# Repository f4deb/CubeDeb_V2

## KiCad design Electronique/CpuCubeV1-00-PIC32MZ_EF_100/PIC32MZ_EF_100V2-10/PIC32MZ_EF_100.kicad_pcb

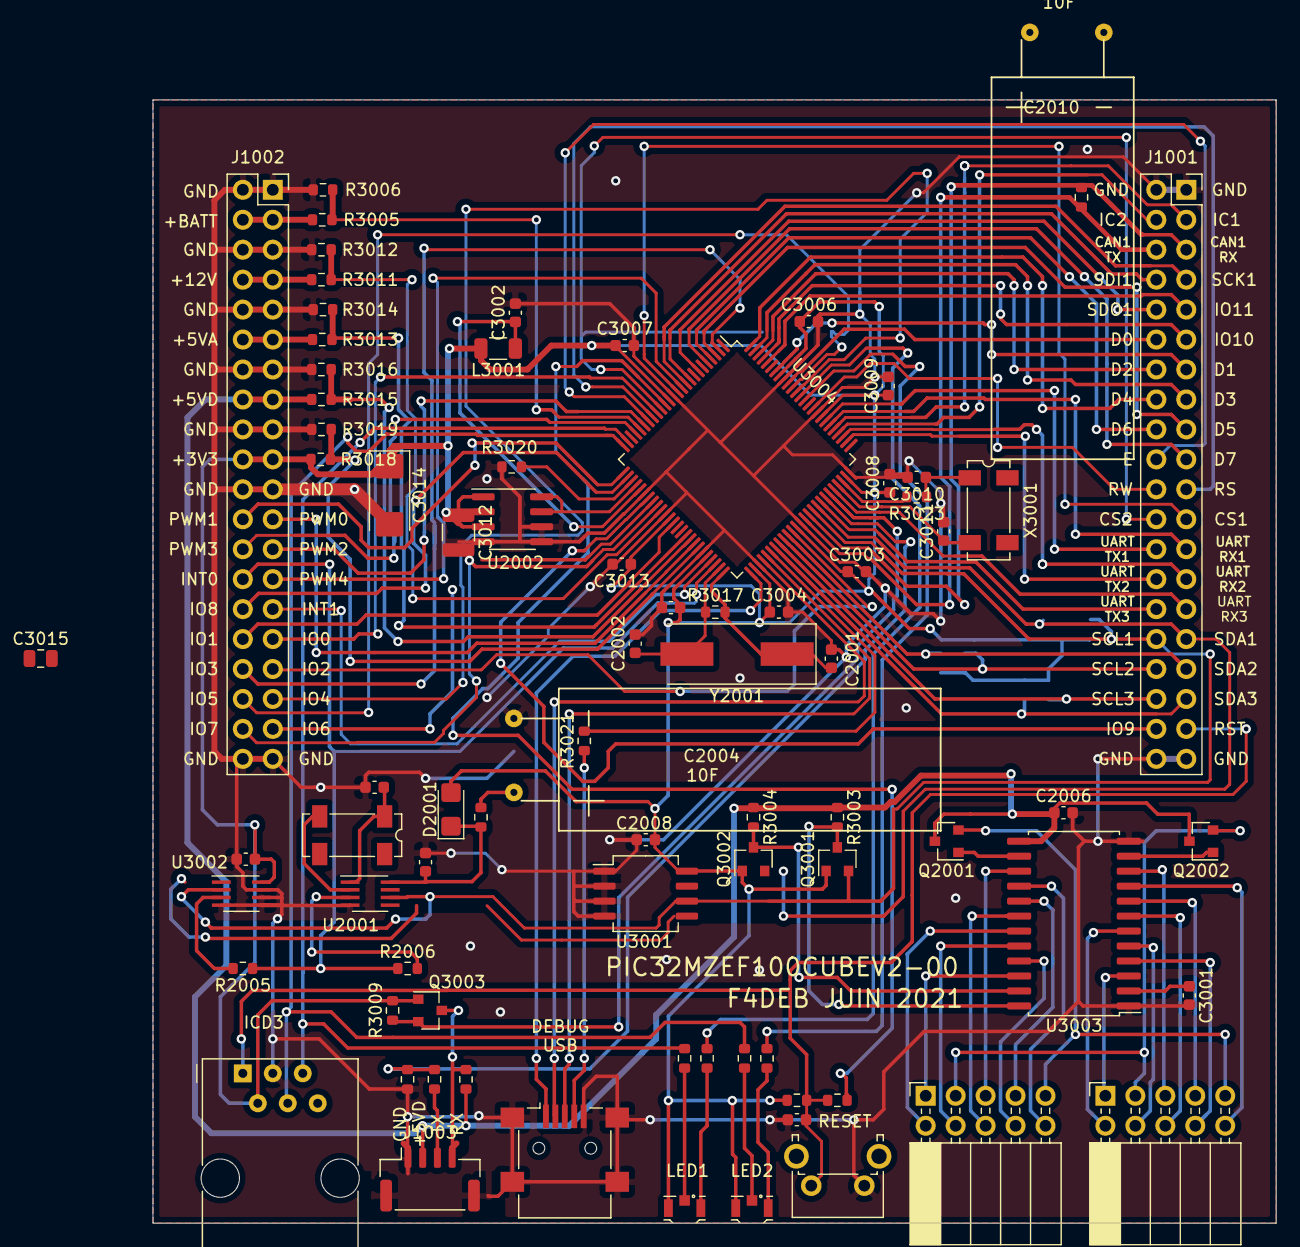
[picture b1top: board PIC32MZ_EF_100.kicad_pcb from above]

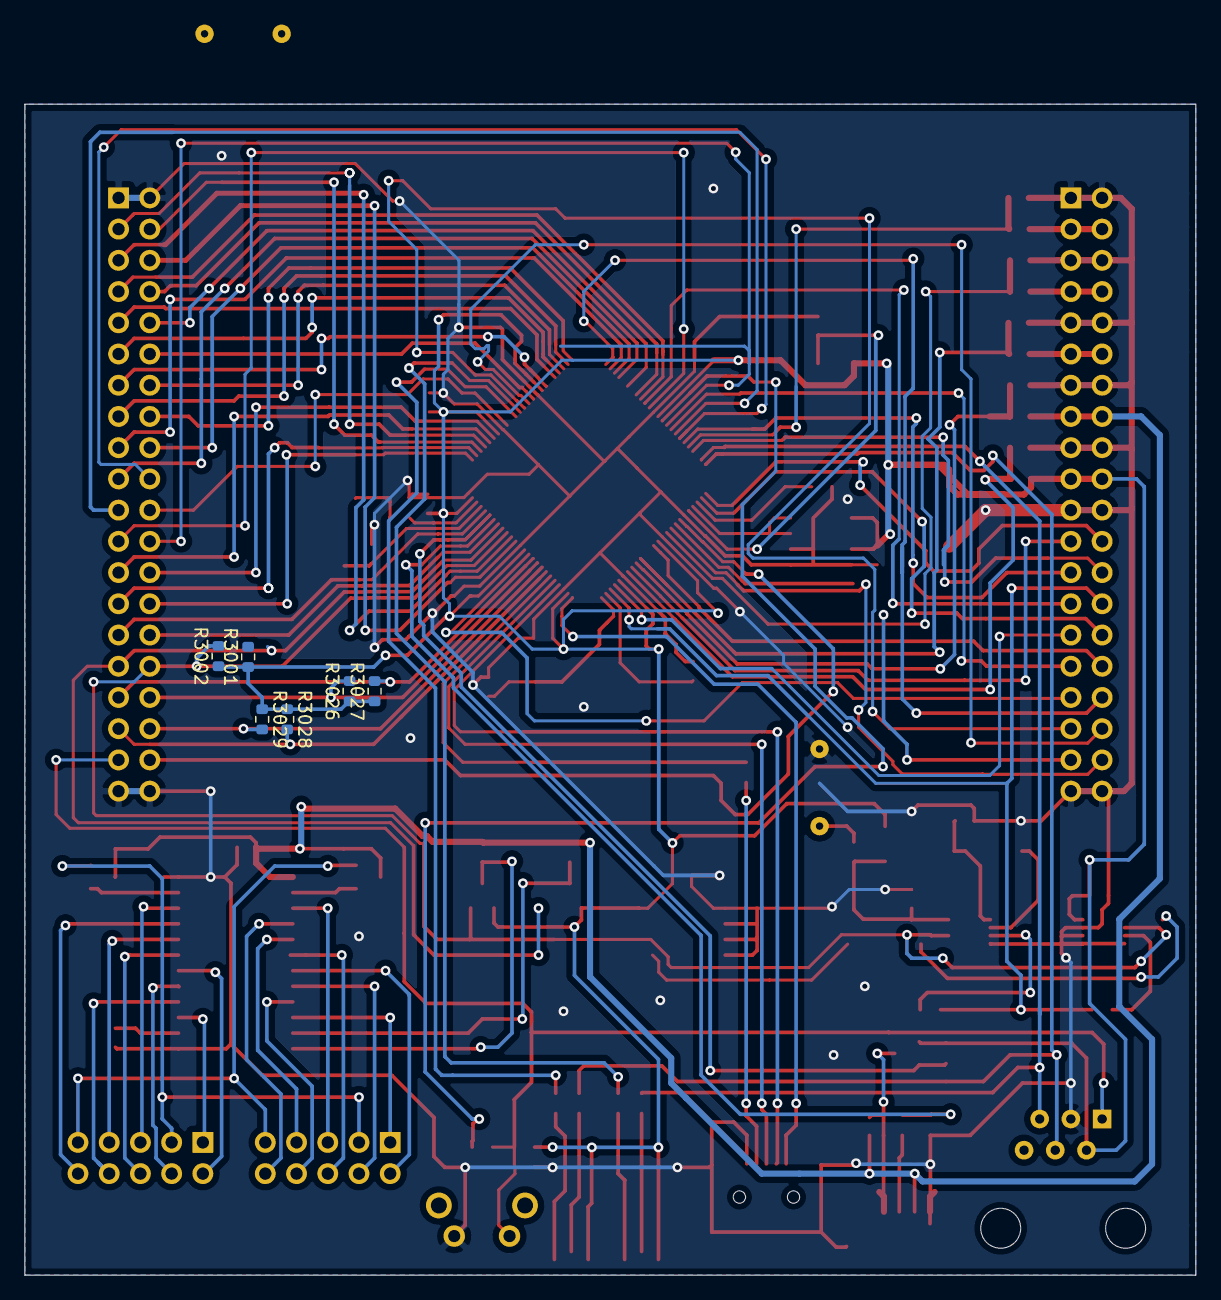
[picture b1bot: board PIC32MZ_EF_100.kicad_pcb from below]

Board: 2 copper layers, 95.2 x 95.2 mm, 87 parts (6 on the bottom side), 120 nets.

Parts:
C2001, C2002: 22p; C_0603_1608Metric
C2003: NC; C_0603_1608Metric
C2004, C2010: 10F; C-10F
C2005: 10p; C_0603_1608Metric
C2006, C2007, C2008, C2009, C3002, C3003, C3004, C3005, C3006, C3007, C3008, C3009, C3013: 100n; C_0603_1608Metric
C3001: 2.7n; C_0603_1608Metric
C3010, C3011: 33p; C_0603_1608Metric
C3012: 2.2µF; C_1210_3225Metric
C3014: 47µ; CP_EIA-6032-28_Kemet-C
C3015: 220p; C_0805_2012Metric
D1001, D1002: LED_Dual_CCA; LED_LiteOn_LTST-S326
D2001: D_Schottky; D_1206_3216Metric_Castellated
J1001, J1002: Conn_02x20_Odd_Even; PinSocket_2x20_P2.54mm_Vertical
J1003: Conn_01x04; JST_GH_SM04B-GHS-TB_1x04-1MP_P1.25mm_Horizontal
J1004: USB_B_Mini; USB_Mini-B_Lumberg_2486_01_Horizontal
J1005: RJ12; RJ12_Amphenol_54601
J2001, J2002: Conn_02x05_Top_Bottom; PinSocket_2x05_P2.54mm_Horizontal
L3001: 15µH; R_1206_3216Metric
Q2001, Q2002: BSR19; SOT-23
Q3001, Q3002, Q3003: 2N7002; SOT-23
R1001, R1002, R1003, R1004: R; R_0603_1608Metric
R2003: 330; R_0603_1608Metric
R2005, R2006, R3022: 100; R_0603_1608Metric
R3001, R3002: 4.7k; R_0603_1608Metric
R3003, R3004: 2.2k; R_0603_1608Metric
R3005, R3009, R3010, R3011, R3013, R3015, R3018, R3025: 10k; R_0603_1608Metric
R3006, R3008, R3012: 1k5; R_0603_1608Metric
R3007: 1k; R_0603_1608Metric
R3014, R3016, R3019: 4k7; R_0603_1608Metric
R3017: 1M; R_0603_1608Metric
R3020, R3021: 0; R_0603_1608Metric
R3023: 2k2; R_0603_1608Metric
R3024: 120; R_0603_1608Metric
R3026, R3027, R3028, R3029: 2k1; R_0603_1608Metric
SW1001: SW_Push; SW_Tactile_SPST_Angled_PTS645Vx58-2LFS
U2001: PCF8563T; SSOP-8_2.95x2.8mm_P0.65mm
U2002: MCP1501-SN; SOIC-8_3.9x4.9mm_P1.27mm
U3001: 24LC1025; SO-8_5.3x6.2mm_P1.27mm
U3002: LM75A; SSOP-8_2.95x2.8mm_P0.65mm
U3003: SAA1064T; SOIC-24W_7.5x15.4mm_P1.27mm
U3004: PIC32MZ2048EF100; TQFP-100_14x14mm_P0.5mm
X3001: 32.768KHz; Crystal_SMD_SeikoEpson_MC306-4Pin_8.0x3.2mm
Y2001: 24Mhz; Crystal_SMD_HC49-SD
Y2003: Crystal; Crystal_SMD_SeikoEpson_MC306-4Pin_8.0x3.2mm

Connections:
+3V3: C2008.1, C2009.1, C3003.1, C3004.1, C3005.1, C3006.1, C3007.1, C3008.1, C3009.1, C3012.1, C3013.1, C3014.1, D1001.3, D1002.3, D2001.2, J1002.19, J1002.20, J1005.2, L3001.2, Q3001.1, Q3002.1, Q3003.1, R3001.1, R3002.1, R3009.2, R3018.1, R3025.1, R3026.1, R3027.1, R3028.1, R3029.1, U2002.1, U2002.3, U3001.8, U3002.8, U3004.14, U3004.37, U3004.46, U3004.52, U3004.62, U3004.74, U3004.83, U3004.93
+5VA: J1002.11, J1002.12, R3013.1
+5VD: C2006.1, J1002.15, J1002.16, J1003.2, Q2001.3, Q2002.3, R3003.1, R3004.1, R3010.1, R3015.1, U3003.13
+12V: J1002.7, J1002.8, R3011.1
+BATT: J1002.3, J1002.4, R3005.1
/CAN1RX: J1001.5, R3024.1, U3004.65
/CAN1TX: J1001.6, R3024.2, U3004.64
/CS1: J1001.23, U3004.12
/CS2: J1001.24, U3004.16
/D0: J1001.12, U3004.91
/D1: J1001.13, U3004.94
/D2: J1001.14, U3004.98
/D3: J1001.15, U3004.99
/D4: J1001.16, U3004.100
/D5: J1001.17, U3004.3
/D6: J1001.18, U3004.4
/D7: J1001.19, U3004.5
/D+: J1004.3, U3004.55
/D-: J1004.2, U3004.54
/E: J1001.20, U3004.19
/I2C/A34: J2001.7, U3003.17
/I2C/B34: J2001.5, U3003.15
/I2C/C34: J2001.6, U3003.18
/I2C/D34: J2001.4, U3003.20
/I2C/E34: J2001.2, U3003.19
/I2C/F34: J2001.1, U3003.22
/I2C/G34: J2001.8, U3003.21
/I2C/P34: J2001.10, U3003.16
/I2C/SDA1: Q3002.2, R3001.2, U2001.5, U3001.5, U3002.1
/IC1: J1001.3, U3004.80
/IC2: J1001.4, U3004.79
/INT0: J1002.28, R2005.1, R2006.1, U3004.48
/INT1: J1002.29, U3004.47
/IO0: J1002.31, U3004.17
/IO1: J1002.32, U3004.38
/IO2: J1002.33, U3004.61
/IO3: J1002.34, U3004.2
/IO4: J1002.35, U3004.89
/IO5: J1002.36, U3004.90
/IO6: J1002.37, U3004.33
/IO7: J1002.38, U3004.34
/IO8: J1002.30, U3004.27
/IO9: J1001.38, U3004.32
/IO10: J1001.11, U3004.97
/IO11: J1001.9, U3004.96
/LED1: R1002.2, U3004.88
/LED2: R1004.2, U3004.87
/PGEC1: J1005.5, R1001.2, U3004.24
/PGED1: J1005.4, R1003.2, U3004.25
/PIC32MZ2048EF100/UART-TX: Q3003.2, R3009.1, U3004.70
/PWM0: J1002.23, U3004.43
/PWM1: J1002.24, U3004.26
/PWM2: J1002.25, U3004.20
/PWM3: J1002.26, U3004.22
/PWM4: J1002.27, U3004.11
/RS: J1001.21, U3004.18
/RST: C2003.1, J1001.37, J1005.1, R3022.1, R3025.2, SW1001.2
/RW: J1001.22, U3004.85
/SCK1: J1001.7, U3004.10
/SCL1: J1001.32, Q3001.2, R3002.2, U2001.6, U3001.6, U3002.2, U3004.66
/SCL2: J1001.34, R3026.2, U3004.59
/SCL3: J1001.36, R3029.2, U3004.58
/SDA1: J1001.31, U3004.67
/SDA2: J1001.33, R3027.2, U3004.60
/SDA3: J1001.35, R3028.2, U3004.57
/SDI1: J1001.8, U3004.9
/SDO1: J1001.10, U3004.7
/UART-RX0: J1003.3, R3007.1
/UART-RX1: J1001.25, U3004.81
/UART-RX2: J1001.27, U3004.78
/UART-RX3: J1001.29, U3004.71
/UART-TX0: J1003.4, Q3003.3, R3010.2
/UART-TX1: J1001.26, U3004.82
/UART-TX2: J1001.28, U3004.77
/UART-TX3: J1001.30, U3004.68
/USBID: J1004.4, R3021.1
/VBUS: J1004.1, U3004.51
GND: C2001.2, C2002.2, C2003.2, C2005.2, C2006.2, C2007.2, C2008.2, C2009.2, C2010.2, C3001.2, C3002.2, C3003.2, C3004.2, C3005.2, C3006.2, C3007.2, C3008.2, C3009.2, C3010.2, C3011.2, C3012.2, C3013.2, C3014.2, C3015.2, J1001.1, J1001.2, J1001.39, J1001.40, J1002.1, J1002.2, J1002.5, J1002.6, J1002.9, J1002.10, J1002.13, J1002.14, J1002.17, J1002.18, J1002.21, J1002.22, J1002.39, J1002.40, J1003.1, J1004.5, J1004.6, J1005.3, R3006.2, R3008.2, R3012.2, R3014.2, R3016.2, R3019.2, R3020.2, SW1001.1, U2001.4, U2002.4, U2002.5, U2002.6, U3001.1, U3001.2, U3001.3, U3001.4, U3002.4, U3002.5, U3002.6, U3002.7, U3003.1, U3003.12, U3004.13, U3004.31, U3004.36, U3004.45, U3004.53, U3004.63, U3004.75, U3004.84, U3004.92
unnamed: C2001.1, R3017.2, U3004.50, Y2001.1
unnamed: C2002.1, R3017.1, U3004.49, Y2001.2
unnamed: C2004.1, R2003.2
unnamed: C2004.2, C2010.1
unnamed: C2005.1, U2001.1, Y2003.1
unnamed: C2007.1, D2001.1, R2003.1, U2001.8
unnamed: C3001.1, U3003.2
unnamed: C3002.1, L3001.1, U3004.30
unnamed: C3010.1, R3023.1, X3001.1
unnamed: C3011.1, U3004.72, X3001.2
unnamed: C3015.1, U2002.7, U2002.8, U3004.29
unnamed: D1001.1, R1002.1
unnamed: D1001.2, R1001.1
unnamed: D1002.1, R1004.1
unnamed: D1002.2, R1003.1
unnamed: J2001.3, J2002.3, Q2002.2
unnamed: J2001.9, J2002.9, Q2001.2
unnamed: J2002.1, U3003.3
unnamed: J2002.2, U3003.6
unnamed: J2002.4, U3003.5
unnamed: J2002.5, U3003.10
unnamed: J2002.6, U3003.7
unnamed: J2002.7, U3003.8
unnamed: J2002.8, U3003.4
unnamed: J2002.10, U3003.9
unnamed: Q2001.1, U3003.14
unnamed: Q2002.1, U3003.11
unnamed: Q3001.3, R3003.2, U3003.24
unnamed: Q3002.3, R3004.2, U3003.23
unnamed: R2005.2, U3002.3
unnamed: R2006.2, U2001.3
unnamed: R3005.2, R3006.1, U3004.21
unnamed: R3007.2, R3008.1, U3004.69
unnamed: R3011.2, R3012.1, U3004.35
unnamed: R3013.2, R3014.1, U3004.41
unnamed: R3015.2, R3016.1, U3004.42
unnamed: R3018.2, R3019.1, U3004.44
unnamed: R3020.1, U3004.28
unnamed: R3021.2, U3004.56
unnamed: R3022.2, U3004.15
unnamed: R3023.2, U3004.73
unnamed: U2001.2, Y2003.2

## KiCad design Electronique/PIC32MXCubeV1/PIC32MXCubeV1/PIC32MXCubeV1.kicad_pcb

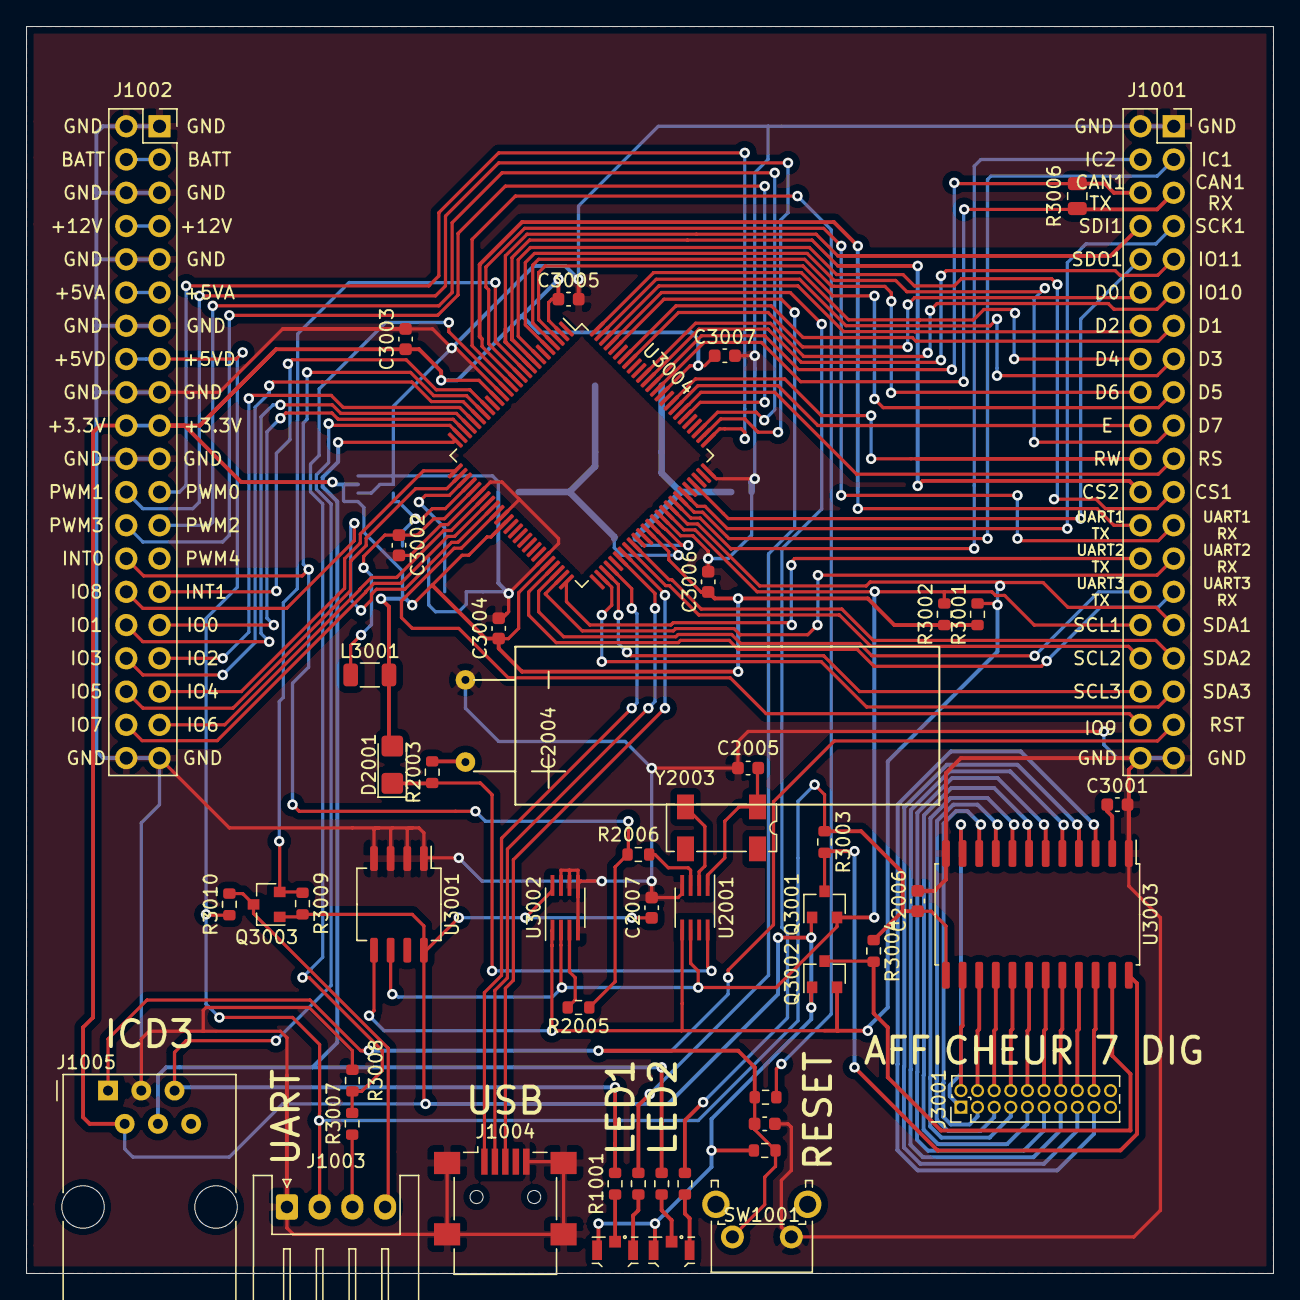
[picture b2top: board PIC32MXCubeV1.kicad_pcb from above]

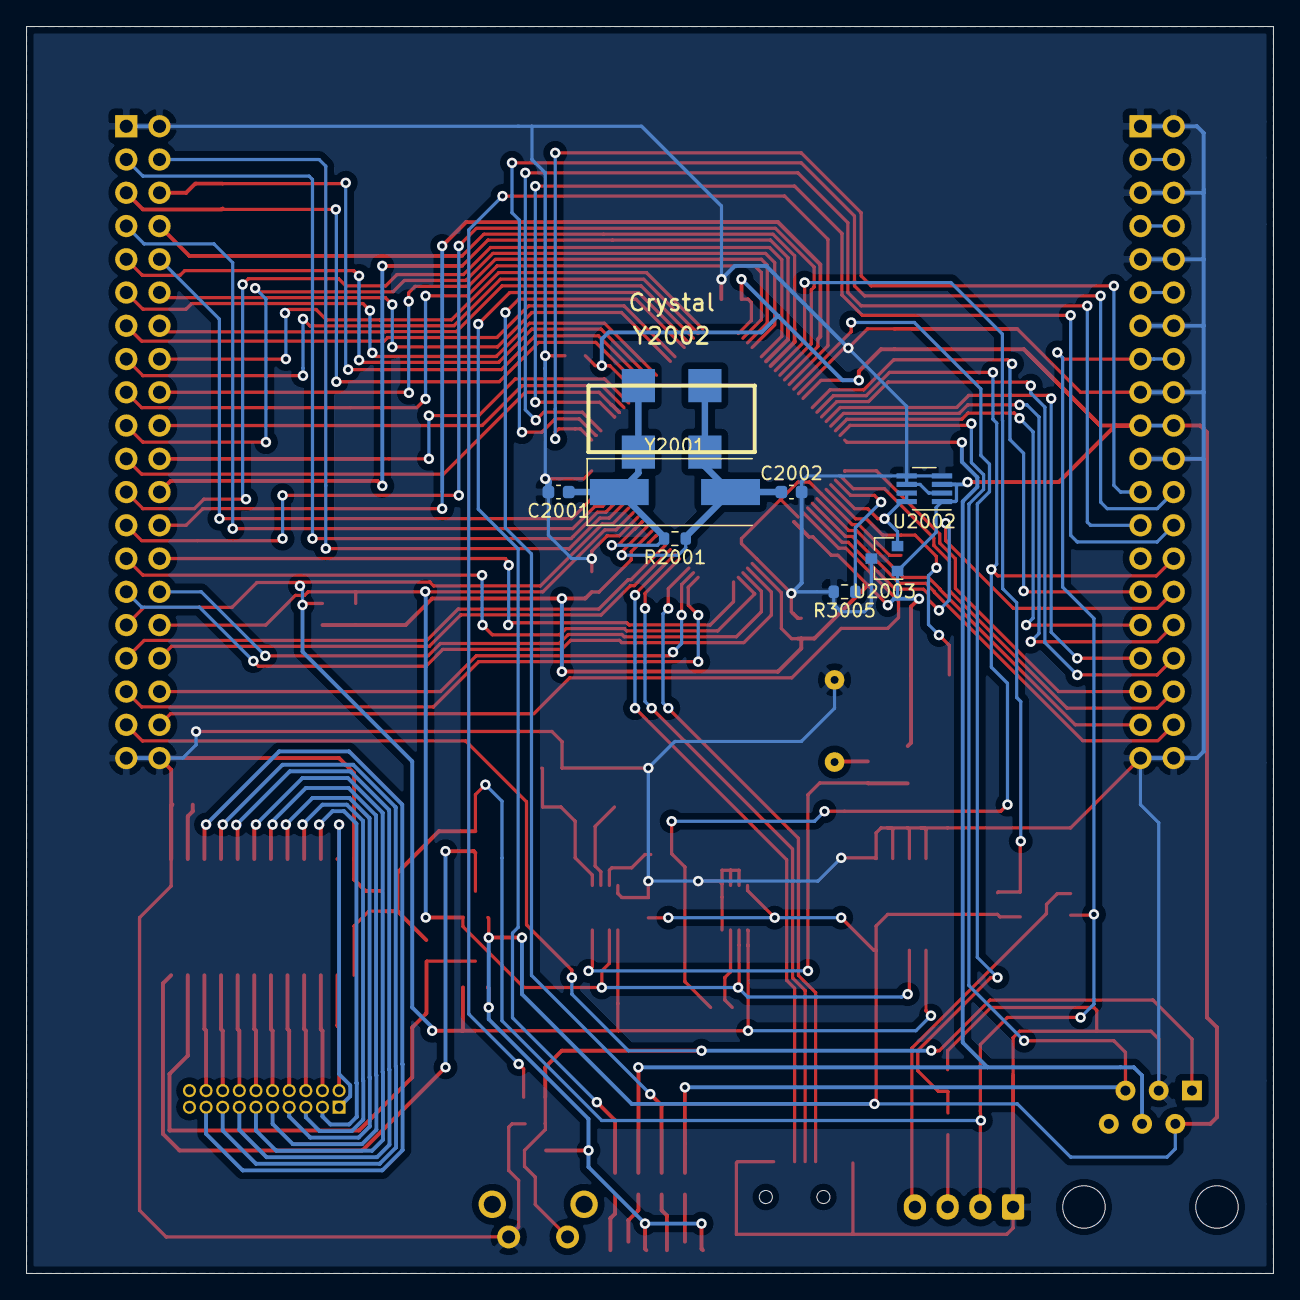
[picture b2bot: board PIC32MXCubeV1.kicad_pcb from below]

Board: 2 copper layers, 95.2 x 95.3 mm, 58 parts (8 on the bottom side), 105 nets.

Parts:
C2001, C2002, C2003: C; C_0603_1608Metric
C2004: CP; C-10F
C2005: 10p; C_0603_1608Metric
C2006, C2007, C3002, C3003, C3004, C3005, C3006, C3007: 100n; C_0603_1608Metric
C3001: 2.7n; C_0603_1608Metric
D1001, D1002: LED_Dual_CCA; LED_LiteOn_LTST-S326
D2001: D_Schottky; D_1206_3216Metric_Castellated
J1001, J1002: Conn_02x20_Odd_Even; PinSocket_2x20_P2.54mm_Vertical
J1003: Conn_01x04; JST_XH_S4B-XH-A_1x04_P2.50mm_Horizontal
J1004: USB_B_Mini; USB_Mini-B_Lumberg_2486_01_Horizontal
J1005: RJ12; RJ12_Amphenol_54601
J3001: Conn_02x10_Odd_Even; PinHeader_2x10_P1.27mm_Vertical
L3001: L; R_1206_3216Metric
Q3001, Q3002, Q3003: 2N7002; SOT-23
R1001, R1002, R1003, R1004, R2001, R2002, R2004, R3007, R3008: R; R_0603_1608Metric
R2003: 330; R_0603_1608Metric
R2005, R2006: 100; R_0603_1608Metric
R3001, R3002: 4.7k; R_0603_1608Metric
R3003, R3004: 2.2k; R_0603_1608Metric
R3005: 0; R_0603_1608Metric
R3006: 120; C_0805_2012Metric
R3009, R3010: 10k; R_0603_1608Metric
SW1001: SW_Push; SW_Tactile_SPST_Angled_PTS645Vx58-2LFS
U2001: PCF8563T; SSOP-8_2.95x2.8mm_P0.65mm
U2002: MCP1501; SOT-23-8_Handsoldering
U2003: REF3020; SOT-23
U3001: 24LC1025; SO-8_5.3x6.2mm_P1.27mm
U3002: LM75A; SSOP-8_2.95x2.8mm_P0.65mm
U3003: SAA1064T; SOIC-24W_7.5x15.4mm_P1.27mm
U3004: PIC32MX795F512L; TQFP-100_14x14mm_P0.5mm
Y2001: Crystal_Small; Crystal_SMD_HC49-SD
Y2002: Crystal; QTZ
Y2003: Crystal; Crystal_SMD_SeikoEpson_MC306-4Pin_8.0x3.2mm

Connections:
+3V3: C2007.1, C3003.1, C3004.1, C3005.1, C3006.1, C3007.1, D1001.3, D1002.3, D2001.2, J1002.19, J1002.20, J1005.2, L3001.2, Q3001.1, Q3002.1, Q3003.1, R2004.1, R3001.1, R3002.1, R3009.2, U2002.1, U2002.3, U2003.1, U3001.8, U3002.8, U3004.2, U3004.16, U3004.37, U3004.46, U3004.62, U3004.86
+5VA: J1002.11, J1002.12
+5VD: C2006.1, J1002.15, J1002.16, J1003.2, R3003.1, R3004.1, R3010.1, U3003.13
+12V: J1002.7, J1002.8
+BATT: J1002.3, J1002.4
/CAN1RX: J1001.5, R3006.2, U3004.87
/CAN1TX: J1001.6, R3006.1, U3004.88
/CS1: J1001.23, U3004.7
/CS2: J1001.24, U3004.8
/D0: J1001.12, U3004.93
/D1: J1001.13, U3004.94
/D2: J1001.14, U3004.98
/D3: J1001.15, U3004.99
/D4: J1001.16, U3004.100
/D5: J1001.17, U3004.3
/D6: J1001.18, U3004.4
/D7: J1001.19, U3004.5
/E: J1001.20, U3004.83
/IC1: J1001.3, U3004.69
/IC2: J1001.4, U3004.68
/INT0: J1002.28, R2005.1, R2006.1, U3004.19
/INT1: J1002.29, U3004.18
/IO0: J1002.31, U3004.23
/IO1: J1002.32, U3004.22
/IO2: J1002.33, U3004.21
/IO3: J1002.34, U3004.20
/IO4: J1002.35, U3004.26
/IO5: J1002.36, U3004.27
/IO6: J1002.37, U3004.32
/IO7: J1002.38, U3004.33
/IO8: J1002.30, U3004.34
/IO9: J1001.38, U3004.35
/IO10: J1001.11, U3004.90
/IO11: J1001.9, U3004.89
/LED1: R1002.2, U3004.96
/LED2: R1004.2, U3004.97
/PGEC1: J1005.5, R1001.2, U3004.24
/PGED1: J1005.4, R1003.2, U3004.25
/PIC32MX795F512L/UART-TX: Q3003.2, R3009.1, U3004.10
/PWM0: J1002.23, U3004.76
/PWM1: J1002.24, U3004.77
/PWM2: J1002.25, U3004.78
/PWM3: J1002.26, U3004.81
/RS: J1001.21, U3004.82
/RST: C2003.1, J1001.37, J1005.1, R2002.1, R2004.2, SW1001.2
/RW: J1001.22, U3004.84
/SCK1: J1001.7, U3004.70
/SCL1: J1001.32, Q3001.2, R3002.2, U2001.6, U3001.6, U3002.2, U3004.66
/SCL2: J1001.34, U3004.58
/SCL3: J1001.36, U3004.53
/SDA1: J1001.31, Q3002.2, R3001.2, U2001.5, U3001.5, U3002.1, U3004.67
/SDA2: J1001.33, U3004.59
/SDA3: J1001.35, U3004.52
/SDI1: J1001.8, U3004.9
/SDO1: J1001.10, U3004.72
/UART-RX0: J1003.3, R3007.1
/UART-RX1: J1001.25, U3004.11
/UART-RX2: J1001.27, U3004.49
/UART-RX3: J1001.29, U3004.47
/UART-TX0: J1003.4, Q3003.3, R3010.2
/UART-TX1: J1001.26, U3004.12
/UART-TX2: J1001.28, U3004.50
/UART-TX3: J1001.30, U3004.48
/USBN: J1004.2, U3004.56
/USBP: J1004.3, U3004.57
/VBUS: J1004.1, U3004.54
GND: C2001.2, C2002.2, C2003.2, C2004.2, C2005.2, C2006.2, C2007.2, C3001.2, C3002.2, C3003.2, C3004.2, C3005.2, C3006.2, C3007.2, J1001.1, J1001.2, J1001.39, J1001.40, J1002.1, J1002.2, J1002.5, J1002.6, J1002.9, J1002.10, J1002.13, J1002.14, J1002.17, J1002.18, J1002.21, J1002.22, J1002.39, J1002.40, J1003.1, J1004.5, J1004.6, J1005.3, R3005.2, R3008.2, SW1001.1, U2001.4, U2002.2, U2002.4, U2002.5, U2002.6, U2003.3, U3001.1, U3001.2, U3001.3, U3001.4, U3002.4, U3002.5, U3002.6, U3002.7, U3003.1, U3003.12, U3004.15, U3004.31, U3004.36, U3004.45, U3004.65, U3004.75
unnamed: C2001.1, R2001.2, U3004.64, Y2001.1, Y2002.1
unnamed: C2002.1, R2001.1, U3004.63, Y2001.2, Y2002.2
unnamed: C2004.1, R2003.2
unnamed: C2005.1, U2001.1, Y2003.1
unnamed: C3001.1, U3003.2
unnamed: C3002.1, L3001.1, U3004.30
unnamed: D1001.1, R1002.1
unnamed: D1001.2, R1001.1
unnamed: D1002.1, R1004.1
unnamed: D1002.2, R1003.1
unnamed: D2001.1, R2003.1, U2001.8
unnamed: J3001.1, U3003.11
unnamed: J3001.2, U3003.14
unnamed: J3001.3, U3003.10
unnamed: J3001.4, U3003.15
unnamed: J3001.5, U3003.9
unnamed: J3001.6, U3003.16
unnamed: J3001.7, U3003.8
unnamed: J3001.8, U3003.17
unnamed: J3001.9, U3003.7
unnamed: J3001.10, U3003.18
unnamed: J3001.11, U3003.6
unnamed: J3001.12, U3003.19
unnamed: J3001.13, U3003.5
unnamed: J3001.14, U3003.20
unnamed: J3001.15, U3003.4
unnamed: J3001.16, U3003.21
unnamed: J3001.17, U3003.3
unnamed: J3001.18, U3003.22
unnamed: Q3001.3, R3003.2, U3003.24
unnamed: Q3002.3, R3004.2, U3003.23
unnamed: R2002.2, U3004.13
unnamed: R2005.2, U3002.3
unnamed: R2006.2, U2001.3
unnamed: R3005.1, U3004.28
unnamed: R3007.2, R3008.1, U3004.14
unnamed: U2001.2, Y2003.2
unnamed: U2002.7, U2002.8, U2003.2, U3004.29

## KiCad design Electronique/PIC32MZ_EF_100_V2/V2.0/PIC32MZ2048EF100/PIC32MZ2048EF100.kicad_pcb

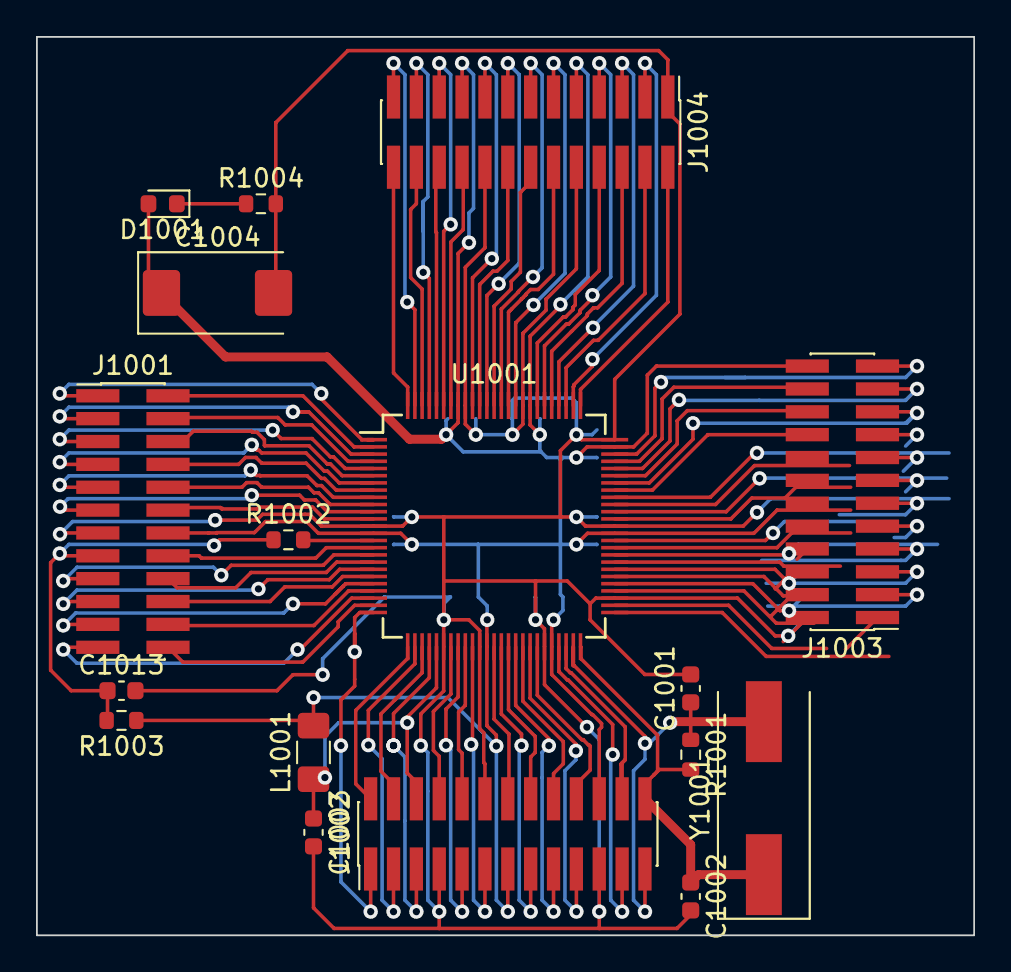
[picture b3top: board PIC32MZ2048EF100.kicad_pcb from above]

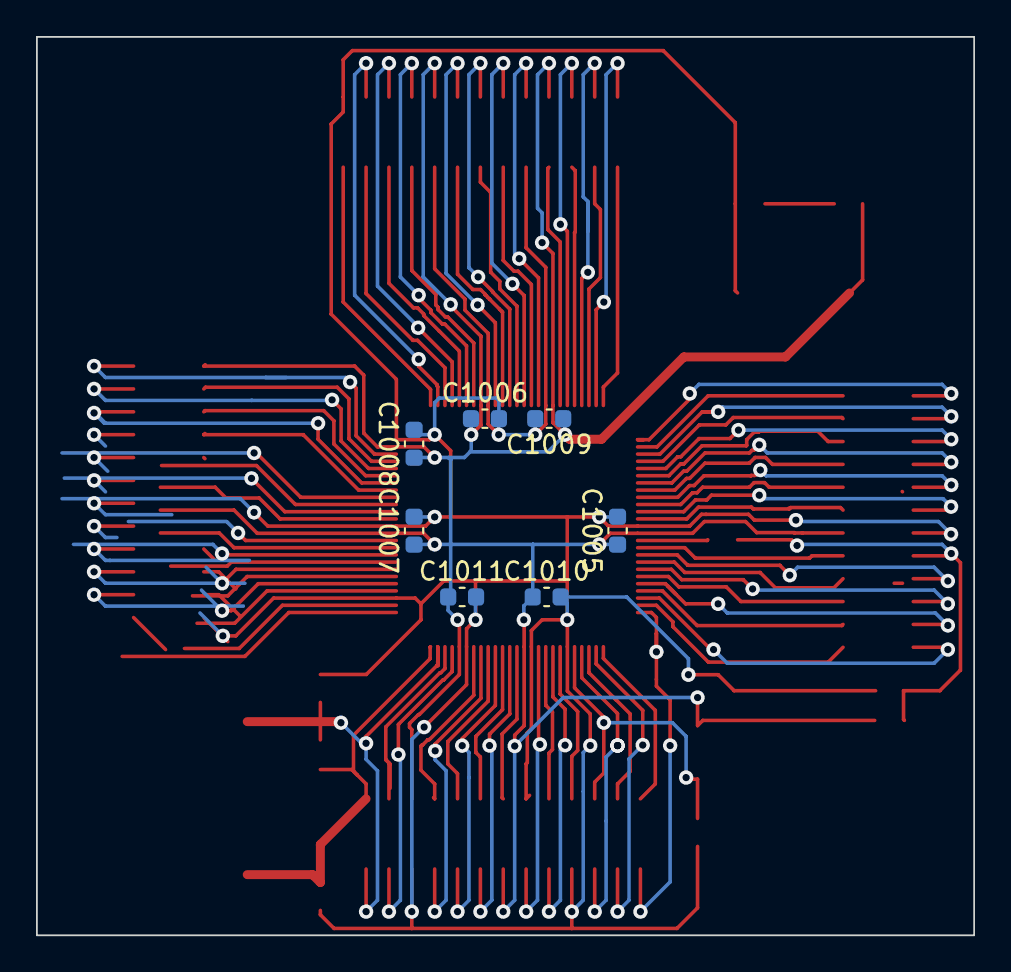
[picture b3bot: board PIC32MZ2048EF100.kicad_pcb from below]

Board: 2 copper layers, 52.1 x 49.9 mm, 24 parts (7 on the bottom side), 88 nets.

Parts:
C1001, C1002, C1003, C1005, C1006, C1007, C1008, C1009, C1010, C1011, C1013: C_0603_1608Metric
C1004: 330µ; CP_EIA-7343-43_Kemet-X
D1001: LED; LED_0603_1608Metric
J1001, J1003: Conn_02x12_Odd_Even; PinHeader_2x12_P1.27mm_Vertical_SMD
J1002, J1004: Conn_02x13_Odd_Even; PinHeader_2x13_P1.27mm_Vertical_SMD
L1001: L_1206_3216Metric_Pad1.42x1.75mm_HandSolder
R1001, R1002, R1003: R_0603_1608Metric
R1004: 330; R_0603_1608Metric
U1001: PIC32MZ2048EFM100; TQFP-100_12x12mm_P0.4mm
Y1001: Crystal_SMD_HC49-SD

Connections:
+3V3: C1004.1, C1005.1, C1006.1, C1007.1, C1008.1, C1009.1, C1010.1, C1011.1, D1001.2 (A), J1001.14, J1002.13, J1002.22, J1003.12, J1003.24, J1004.9, J1004.19, L1001.2, R1003.1, U1001.14 (VDD), U1001.37 (VDD), U1001.46 (VDD), U1001.62 (VDD), U1001.74 (VDD), U1001.83 (VDD), U1001.93 (VDD)
/1: J1001.1, U1001.1 (AN23/AERXERR/RG15)
/2: J1001.2, U1001.2 (EBIA5/AN34/PMA5/RA5)
/3: J1001.3, U1001.3 (EBID5/AN17/RPE5/PMD5/RE5)
/4: J1001.4, U1001.4 (EBID6/AN16/PMD6/RE6)
/5: J1001.5, U1001.5 (EBID7/AN15/PMD7/RE7)
/6: J1001.6, U1001.6 (EBIA6/AN22/RPC1/PMA6/RC1)
/7: J1001.7, U1001.7 (EBIA12/AN21/RPC2/PMA12/RC2)
/8: J1001.8, U1001.8 (EBIWE/AN20/RPC3/PMWR/RC3)
/9: J1001.9, U1001.9 (EBIOE/AN19/RPC4/PMRD/RC4)
/10: J1001.10, U1001.10 (AN14/C1IND/ECOL/RPG6/SCK2/RG6)
/11: J1001.11, U1001.11 (EBIA4/AN13/C1INC/ECRS/RPG7/SDA4/PMA4/RG7)
/12: J1001.12, U1001.12 (EBIA3/AN12/C2IND/ERXDV/ECRSDV/AERXDV/_A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)
/15: C1013.1, J1001.15, R1002.1, R1003.2
/16: J1001.16, U1001.16 (EBIA2/AN11/C2INC/ERXCLK/EREFCLK/AERXCLK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)
/17: J1001.17, U1001.17 (TMS/EBIA16/AN24/RA0)
/18: J1001.18, U1001.18 (AN25/AERXD0/RPE8/RE8)
/19: J1001.19, U1001.19 (AN26/AERXD1/RPE9/RE9)
/20: J1001.20, U1001.20 (AN45/C1INA/RPB5/RB5)
/21: J1001.21, U1001.21 (AN4/C1INB/RB4)
/22: J1001.22, U1001.22 (AN3/C2INA/RPB3/RB3)
/23: J1001.23, U1001.23 (AN2/C2INB/RPB2/RB2)
/24: J1001.24, U1001.24 (PGEC1/AN1/RPB1/RB1)
/25: J1002.1, U1001.25 (PGED1/AN0/RPB0/RB0)
/26: J1002.2, U1001.26 (PGEC2/AN46/RPB6/RB6)
/27: J1002.3, U1001.27 (PGED2/AN47/RPB7/RB7)
/28: J1002.4, U1001.28 (VREF-/CVREF-/AN27/AERXD2/RA9)
/29: J1002.5, U1001.29 (VREF+/CVREF+/AN28/AERXD3/RA10)
/30: C1003.1, J1002.6, L1001.1, U1001.30 (AVDD)
/32: J1002.8, U1001.32 (EBIA10/AN48/RPB8/PMA10/RB8)
/33: J1002.9, U1001.33 (EBIA7/AN49/RPB9/PMA7/RB9)
/34: J1002.10, U1001.34 (EBIA13/CVREFOUT/AN5/RPB10/PMA13/RB10)
/35: J1002.11, U1001.35 (AN6/ERXERR/AETXERR/RB11)
/38: J1002.14, U1001.38 (TCK/EBIA19/AN29/RA1)
/39: J1002.15, U1001.39 (TDI/EBIA18/AN30/RPF13/SCK5/RF13)
/40: J1002.16, U1001.40 (TDO/EBIA17/AN31/RPF12/RF12)
/41: J1002.17, U1001.41 (EBIA11/AN7/ERXD0/AECRS/PMA11/RB12)
/42: J1002.18, U1001.42 (AN8/ERXD1/AECOL/RB13)
/43: J1002.19, U1001.43 (EBIA1/AN9/ERXD2/AETXD3/RPB14/SCK3/PMA1/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)
/44: J1002.20, U1001.44 (EBIA0/AN10/ERXD3/AETXD2/RPB15/OCFB/PMA0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)
/47: J1002.23, U1001.47 (AN32/AETXD0/RPD14/RD14)
/48: J1002.24, U1001.48 (AN33/AETXD1/RPD15/SCK6/RD15)
/49: C1001.1, J1002.25, R1001.1, U1001.49 (OSC1/CLKI/RC12), Y1001.2
/50: C1002.1, J1002.26, R1001.2, U1001.50 (OSC2/CLKO/RC15), Y1001.1
/51: J1003.1, U1001.51 (VBUS)
/52: J1003.2, U1001.52 (VUSB3V3)
/54: J1003.4, U1001.54 (D-)
/55: J1003.5, U1001.55 (D+)
/56: J1003.6, U1001.56 (RPF3/USBID/RF3)
/57: J1003.7, U1001.57 (EBIRDY3/RPF2/SDA3/RF2)
/58: J1003.8, U1001.58 (EBIRDY2/RPF8/SCL3/RF8)
/59: J1003.9, U1001.59 (EBICS0/SCL2/RA2)
/60: J1003.10, U1001.60 (EBIRDY1/SDA2/RA3)
/61: J1003.11, U1001.61 (EBIA14/PMCS1/PMA14/RA4)
/64: J1003.14, U1001.64 (EBIA9/RPF4/SDA5/PMA9/RF4)
/65: J1003.15, U1001.65 (EBIA8/RPF5/SCL5/PMA8/RF5)
/66: J1003.16, U1001.66 (AETXCLK/RPA14/SCL1/RA14)
/67: J1003.17, U1001.67 (AETXEN/RPA15/SDA1/RA15)
/68: J1003.18, U1001.68 (EBIA15/RPD9/PMCS2/PMA15/RD9)
/69: J1003.19, U1001.69 (RPD10/SCK4/RD10)
/70: J1003.20, U1001.70 (EMDC/AEMDC/RPD11/RD11)
/71: J1003.21, U1001.71 (EMDIO/AEMDIO/RPD0/RTCC/INT0/RD0)
/72: J1003.22, U1001.72 (SOSCI/RPC13/RC13)
/73: J1003.23, U1001.73 (SOSCO/RPC14/T1CK/RC14)
/76: J1004.2, U1001.76 (RPD1/SCK1/RD1)
/77: J1004.3, U1001.77 (EBID14/ETXEN/RPD2/PMD14/RD2)
/78: J1004.4, U1001.78 (EBID15/ETXCLK/RPD3/PMD15/RD3)
/79: J1004.5, U1001.79 (EBID12/ETXD2/RPD12/PMD12/RD12)
/80: J1004.6, U1001.80 (EBID13/ETXD3/PMD13/RD13)
/81: J1004.7, U1001.81 (SQICS0/RPD4/RD4)
/82: J1004.8, U1001.82 (SQICS1/RPD5/RD5)
/85: J1004.11, U1001.85 (EBID11/ETXD1/RPF0/PMD11/RF0)
/86: J1004.12, U1001.86 (EBID10/ETXD0/RPF1/PMD10/RF1)
/87: J1004.13, U1001.87 (EBID9/ETXERR/RPG1/PMD9/RG1)
/88: J1004.14, U1001.88 (EBID8/RPG0/PMD8/RG0)
/89: J1004.15, U1001.89 (TRCLK/SQICLK/RA6)
/90: J1004.16, U1001.90 (TRD3/SQID3/RA7)
/91: J1004.17, U1001.91 (EBID0/PMD0/RE0)
/94: J1004.20, U1001.94 (EBID1/PMD1/RE1)
/95: J1004.21, U1001.95 (TRD2/SQID2/RG14)
/96: J1004.22, U1001.96 (TRD1/SQID1/RG12)
/97: J1004.23, U1001.97 (TRD0/SQID0/RG13)
/98: J1004.24, U1001.98 (EBID2/PMD2/RE2)
/99: J1004.25, U1001.99 (EBID3/RPE3/PMD3/RE3)
/100: J1004.26, U1001.100 (BID4/AN18/PMD4/RE4)
GND: C1001.2, C1002.2, C1003.2, C1004.2, C1005.2, C1006.2, C1007.2, C1008.2, C1009.2, C1010.2, C1011.2, C1013.2, J1001.13, J1002.7, J1002.12, J1002.21, J1003.3, J1003.13, J1004.1, J1004.10, J1004.18, R1004.2, U1001.13 (VSS), U1001.31 (AVSS), U1001.36 (VSS), U1001.45 (VSS), U1001.53 (VSS), U1001.63 (VSS), U1001.75 (VSS), U1001.84 (VSS), U1001.92 (VSS)
unnamed: D1001.1 (K), R1004.1
unnamed: R1002.2, U1001.15 (MCLR)
